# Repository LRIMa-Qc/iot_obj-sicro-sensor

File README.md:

# iot_obj-sicro-sensor

Authors : LRIMa (Laboratoire de Recherche Informatique de Maisonneuve)

## Repo composition

```bash
code/
├── actioneur       (esp32 code)
├── broadcaster     (sensor code [nrf52833])
├── central         (python BLE scanning and ALIVEcode integration)
└── central-nrf     (BLE receiver [nrf52840dongle])
schematic/
├── lrima-main/     (Main board KiCad project)
└── lrima-ground/   (Ground board KiCad project)
models/
└── sensor-casing/  (3D CAD models for enclosure)
```

### Physical device

The schematics and PCB were designed using [KiCad](https://www.kicad.org/) EDA software
There is a protective layer that needs to be applied on the ground part of the pcb to prevent corrosion

## Building

#### Tools needed

- VS Code
- [nRF Connect](https://www.nordicsemi.com/Products/Development-tools/nrf-connect-for-desktop)
- [nRF Connect VS Code extension](https://www.nordicsemi.com/Products/Development-tools/nRF-Connect-for-VS-Code)
- nRF toolchain `v3.2.4`
- nRF SDK `v3.2.4`
- J-Link
- Python 3.8+ (for central application)

#### Broadcaster

##### Preparing the environment

Before building the broadcaster program, you **must** make sure that you changed the `CONFIG_BLE_USER_DEFINED_MAC_ADDR` and the `CONFIG_BLE_USER_DEFINED_NAME` so that they are unique. Note that the `CONFIG_BLE_USER_DEFINED_NAME` must end with a number (ex : 01). If you need mac address, you can use this [mac address generator](https://dnschecker.org/mac-address-generator.php).

##### Building

The broadcaster uses the **sysbuild** system from NCS v3.2.4. To build the program for the nrf52833 using the [nRF Connect VS Code extension](https://www.nordicsemi.com/Products/Development-tools/nRF-Connect-for-VS-Code):

1. Open the broadcaster folder in VS Code
2. Use the nRF Connect extension to build using the `lrima_greenhouse_nrf52833` board
3. Flash using the [extension flashing options](https://nrfconnect.github.io/vscode-nrf-connect/get_started/quick_debug.html#how-to-flash-an-application)

Note: If flashing fails, use the `erase and flash` option to perform a full erase first.

###### J-Link setup

#### Firmware over the air update (DFU)

The board supports over-the-air firmware updates. To prepare an update:

1. Build the application as described above
2. Locate the signed image in the sysbuild app domain: `build/broadcaster/zephyr/zephyr.signed.bin`
3. Transfer this file to your phone
4. Press and hold button1 until the LED is on, then release
5. You will have up to 60 seconds (configurable via `CONFIG_BLE_DFU_ADV_DURATION_SEC`) to start the update
6. Use the [nRF Connect mobile app](https://www.nordicsemi.com/Products/Development-tools/nrf-connect-for-mobile) to connect to the device (named with your `CONFIG_BLE_USER_DEFINED_NAME`)
7. Go to the `DFU` tab and select `zephyr.signed.bin`
8. Press `Upload` and monitor the progress

#### Device Functionality

The broadcaster uses a single BLE advertising workflow. It sends sensor data uplink and then opens a short scan window to receive a downlink sleep update when needed. The user can wake up the device at any time by pressing button1. There is never a connection established, and all communication is done through advertisements and scan responses.

##### Broadcaster

The broadcaster collects sensor data and transmits it BLE advertisements:

**Supported sensors:**

- Temperature/Humidity (SHT4X)
- Soil temperature/moisture/conductivity (STCC4)
- CO2 concentration

**Transmission behavior:**

- Sends data at intervals specified by `CONFIG_SENSOR_SLEEP_DURATION_SEC`
- Uses BLE advertising for the duration specified in `CONFIG_BLE_ADV_DURATION_SEC`
- Publishes a 29-byte service payload containing company ID, node ID, sequence, sleep duration, sensor values, and a presence bitmap
- Opens an active scan window after uplink to receive sleep updates sent by the central
- Beacon payload structure is shown below:

> **Note:** The diagram above predates the latest payload format. See the broadcaster documentation for the full 29-byte layout and presence bitmap details.

### Central-nrf

The central-nrf firmware runs on the nRF52840 dongle to receive BLE broadcasts from the broadcaster.

**Building:**

1. Use the [nRF Connect VS Code extension](https://www.nordicsemi.com/Products/Development-tools/nRF-Connect-for-VS-Code) to build for `nrf52840dongle_nrf52840` board
2. Flash using the nRF Connect for Desktop programmer tools
3. Put the device in [DFU mode](https://infocenter.nordicsemi.com/index.jsp?topic=%2Fug_nrf52840_dongle%2FUG%2Fnrf52840_Dongle%2Fprogramming.html)
4. Flash the `build/zephyr/zephyr.hex` file

### Central (Python Application)

The central application handles BLE scanning, data collection, and integration with ALIVEcode.

**Core modules:**

- `core/storage.py` - Persistent data management
- `core/payload.py` - Sensor data parsing and validation
- `core/aliot_sync.py` - ALIVEcode cloud integration
- `core/downlink_advertiser.py` - BlueZ D-Bus advertiser for sleep-time downlink frames
- `core/health.py` - System health monitoring
- `core/config.py` - Configuration management

**Setup and running:**

1. Plug the Central-nrf dongle into a computer or Raspberry Pi
2. Configure the application:
   - Copy `config.ini.example` to `config.ini`
   - Set your `object_id` and `auth_token` from your [ALIVEcode.ca](https://ALIVEcode.ca) IoT project

3. Install dependencies:

   ```bash
   # For Raspberry Pi 4
   pip install -r requirements_pi4.txt

   # For Raspberry Pi 5
   pip install -r requirements_pi5.txt
   ```

   (Using a Python virtual environment is recommended)

   `dbus-next` is required because downlink sleep updates are emitted through BlueZ D-Bus advertising APIs.

4. Run the application:

   ```bash
   python main.py
   ```

5. Power on the broadcaster devices

The application will automatically scan for broadcaster devices, collecting sensor data and synchronizing with ALIVEcode.
It publishes each node under `/doc/<device_index>` including `/doc/<device_index>/sleep_duration_sec`, and uses `/doc/sleep_time` as the desired target for downlink sleep updates.

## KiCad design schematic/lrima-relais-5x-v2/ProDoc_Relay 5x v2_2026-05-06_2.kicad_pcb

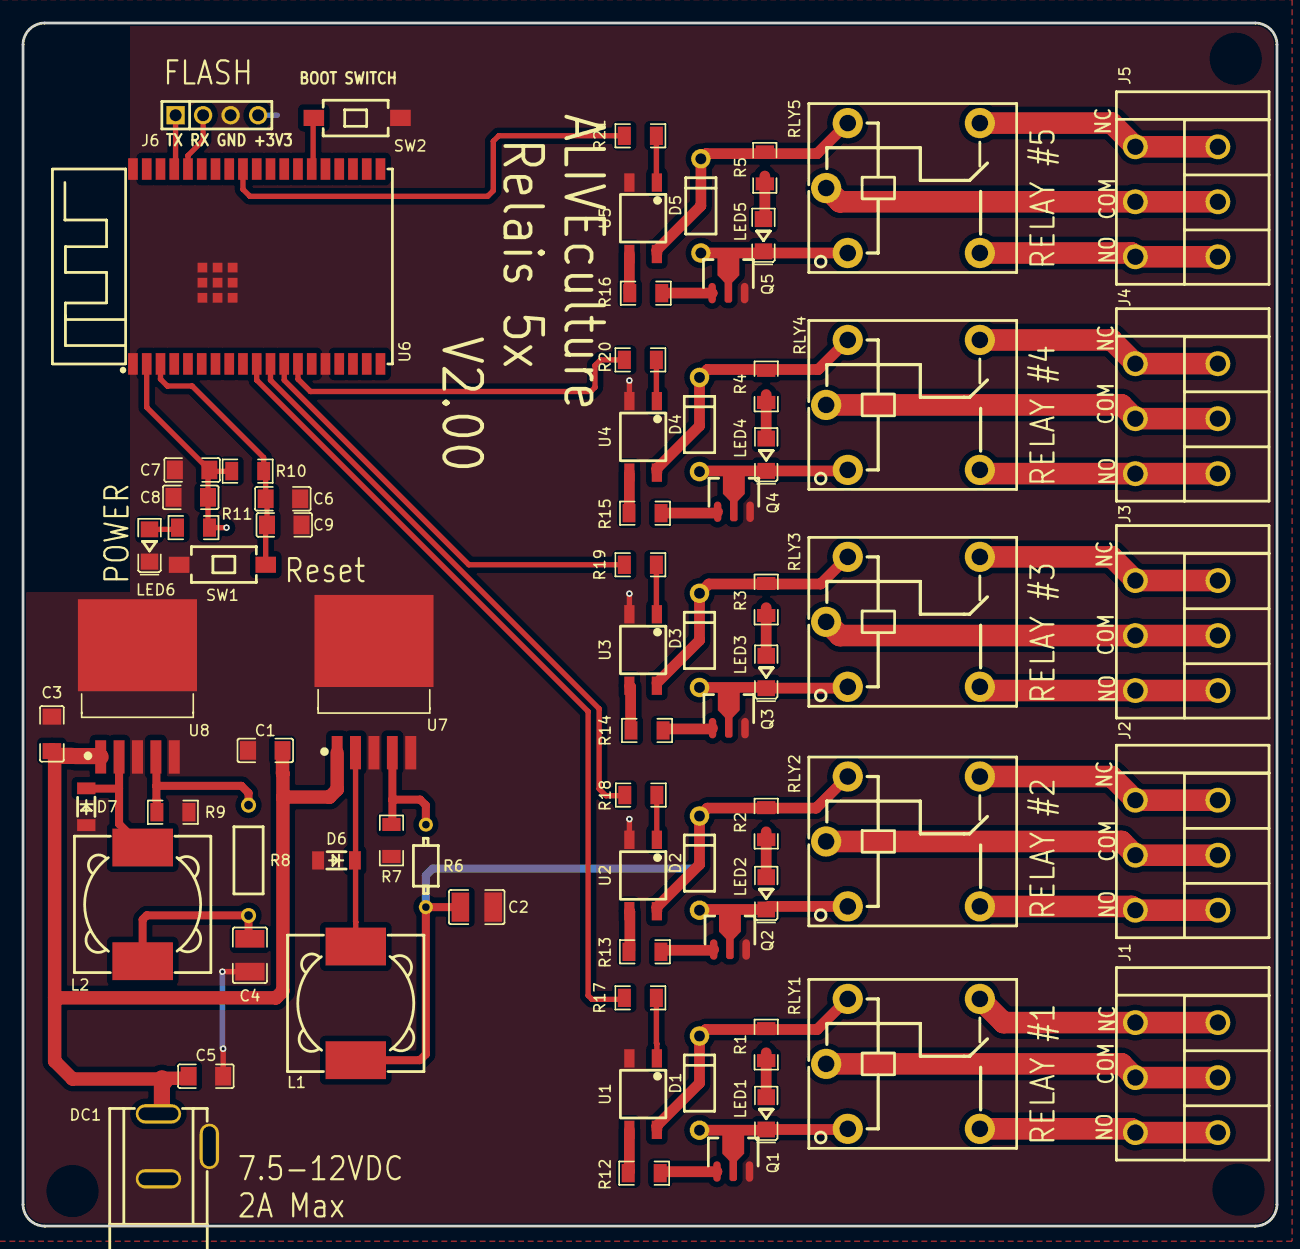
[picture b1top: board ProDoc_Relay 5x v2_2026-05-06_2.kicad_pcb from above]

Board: 2 copper layers, 115.8 x 111.1 mm, 72 parts (0 on the bottom side), 43 nets.

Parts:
C1, C3, C5, C6, C7, C8, C9: C1206
C2, C4: C1210
D1, D2, D3, D4, D5: DO-41_BD2.4-L4.7-P8.70-D0.9-RD
D6, D7: LL-34_L3.5-W1.5-RD
DC1: CONN-TH_DC-005-2.5A-2.0
J1, J2, J3, J4, J5: CONN-TH_3P-P5.08_DIBO_DB142R-5.08-3P
J6: HDR-TH_4P-P2.54-V-M
L1, L2: IND-SMD_L12.5-W12.5_B82477P4XX
LED1, LED2, LED3, LED4, LED5, LED6: LED1206-R-RD_RED
Q1, Q2, Q3, Q4, Q5: SOT-89-3_L4.5-W2.5-P1.50-LS4.2-TR
R1, R2, R3, R4, R5, R7, R9, R10, R11, R12, R13, R14, R15, R16, R17, R18, R19, R20, R21: R1206
R6: RES-TH_BD2.3-L3.7-P7.70-D0.9
R8: RES-TH_BD2.7-L6.2-P10.20-D0.4
RLY1, RLY2, RLY3, RLY4, RLY5: RELAY-TH_SRD-XXVDC-XL-C
SW1, SW2: SW-SMD_L6.0-W3.3-LS8.0
U1, U2, U3, U4, U5: OPTO-SMD-4_L4.4-W4.1-P2.54-LS7.0-TL
U6: WIFI-SMD_ESP32-WROVER-IE8MB
U7, U8: TO-263-5_L10.2-W8.9-P1.70-BR

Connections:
$1N1874: LED1.1, R1.1
$1N2733: LED2.1, R2.1
$1N2848: LED3.1, R3.1
$1N2963: LED4.1, R4.1
$1N3078: LED5.1, R5.1
$1N7448: D6.1, L1.2, U7.2
$1N7557: R6.2, R7.2, U7.4
$1N7965: D7.1, L2.2, U8.2
$1N7972: R8.2, R9.2, U8.4
$1N9867: SW2.1, U6.25
$1N10273: LED6.1, R11.1
$1N20678: R12.1, U1.3
$1N20720: R13.1, U2.3
$1N20762: R14.1, U3.3
$1N20804: R15.1, U4.3
$1N20846: R16.1, U5.3
$1N25591: R17.2, U1.1
$1N25607: R18.2, U2.1
$1N25612: R19.2, U3.1
$1N25623: R20.2, U4.1
$1N25628: R21.2, U5.1
+3V3: C4.1, C7.2, C8.2, J6.4, L2.1, R8.1, R10.2, R11.2, U6.2
+5V: C2.1, D1.1, D2.1, D3.1, D4.1, D5.1, L1.1, R1.2, R2.2, R3.2, R4.2, R5.2, R6.1, RLY1.4, RLY2.4, RLY3.4, RLY4.4, RLY5.4, U1.4, U2.4, U3.4, U4.4, U5.4
GND: C1.1, C2.2, C3.1, C4.2, C5.2, C6.2, C7.1, C8.1, C9.1, D6.2, D7.2, DC1.2, DC1.3, J6.3, LED6.2, Q1.3, Q2.3, Q3.3, Q4.3, Q5.3, R7.1, R9.1, SW1.2, SW2.2, U1.2, U2.2, U3.2, U4.2, U5.2, U6.1, U6.15, U6.38, U7.3, U7.5, U7.6, U8.3, U8.5, U8.6
RE1-ACT: R17.1, U6.10
RE1-COIL: Q1.1, R12.2
RE1-COIL-END: D1.2, LED1.2, Q1.2, RLY1.1
RE2-ACT: R18.1, U6.11
RE2-COIL: Q2.1, R13.2
RE2-COIL-END: D2.2, LED2.2, Q2.2, RLY2.1
RE3-ACT: R19.1, U6.12
RE3-COIL: Q3.1, R14.2
RE3-COIL-END: D3.2, LED3.2, Q3.2, RLY3.1
RE4-ACT: R20.1, U6.13
RE4-COIL: Q4.1, R15.2
RE4-COIL-END: D4.2, LED4.2, Q4.2, RLY4.1
RE5-ACT: R21.1, U6.30
RE5-COIL: Q5.1, R16.2
RE5-COIL-END: D5.2, LED5.2, Q5.2, RLY5.1
RST: C6.1, C9.2, R10.1, SW1.1, U6.3
RX: J6.2, U6.34
TX: J6.1, U6.35
VIN: C1.2, C3.2, C5.1, DC1.1, U7.1, U8.1

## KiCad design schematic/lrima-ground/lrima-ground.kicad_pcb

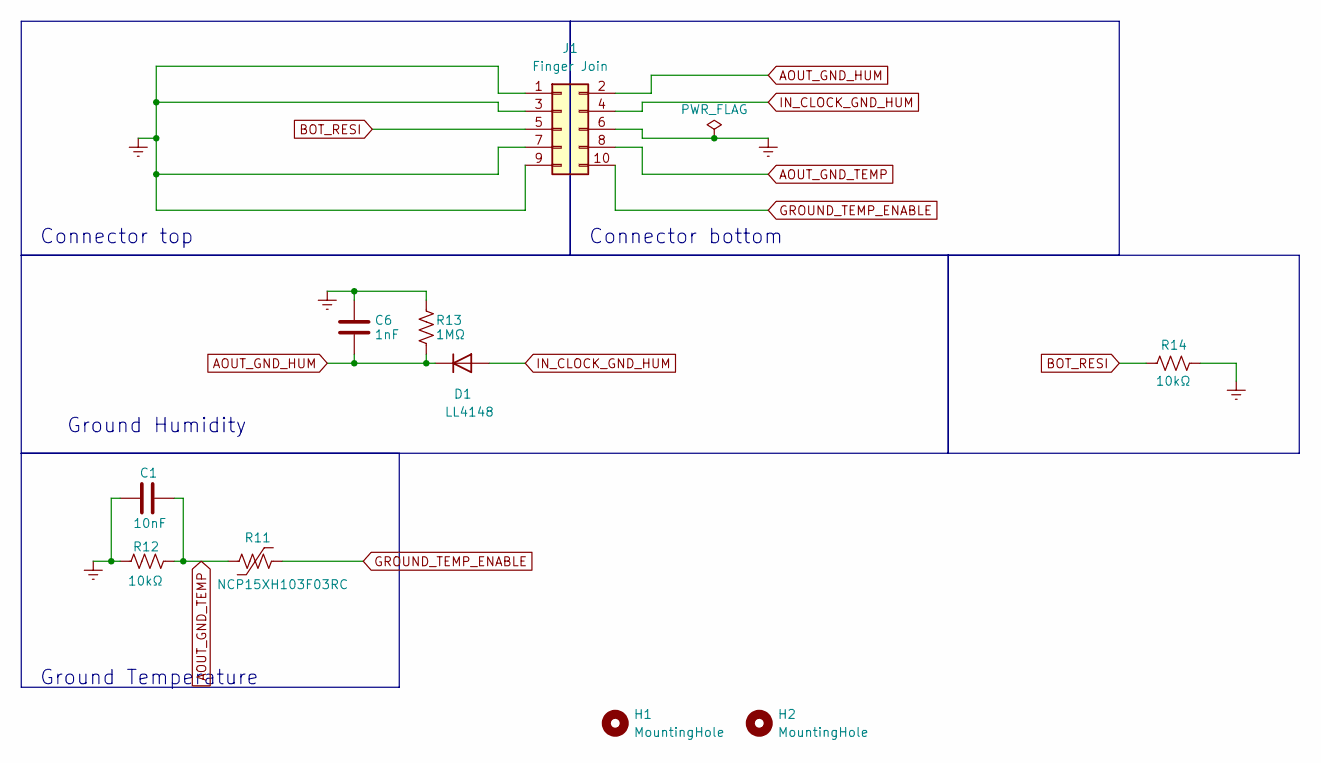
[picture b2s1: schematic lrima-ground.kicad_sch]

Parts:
C1: 10nF; C_0603_1608Metric; Manufacturer Part CC0603KRX7R9BB103; LCSC Part Name 10nF ±10% 50V
C6: 1nF; C_0603_1608Metric; Manufacturer Part CC0603KRX7R9BB102; LCSC Part Name 1nF ±10% 50V
D1: LL4148; D_MiniMELF; Manufacturer Part LL4148; LCSC Part Name 75V 200mA 4ns
H1, H2: MountingHole; MountingHole_3.2mm_M3
J1: Finger Join; Edge_Finger_5P
R11: NCP15XH103F03RC; R_0402_1005Metric; Manufacturer Part NCP15XH103F03RC; LCSC Part Name 10kΩ 电阻精度:±1% 3380K
R12, R14: 10kΩ; R_0603_1608Metric; Manufacturer Part 0603WAF1002T5E; LCSC Part Name 厚膜电阻 10kΩ ±1% 100mW
R13: 1MΩ; R_0603_1608Metric; Manufacturer Part 0603WAF1004T5E; LCSC Part Name 1MΩ ±1% 100mW

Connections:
AOUT_GND_HUM: C6.1, D1.1 (K), J1.2, R13.1
AOUT_GND_TEMP: C1.2, J1.8, R11.1, R12.2
BOT_RESI: J1.5, R14.1
GNDREF: C1.1, C6.2, J1.1, J1.3, J1.6, J1.7, J1.9, R12.1, R13.2, R14.2
GROUND_TEMP_ENABLE: J1.10, R11.2
IN_CLOCK_GND_HUM: D1.2 (A), J1.4

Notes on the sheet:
Ground Temperature
Connector top
Connector bottom
Ground Humidity

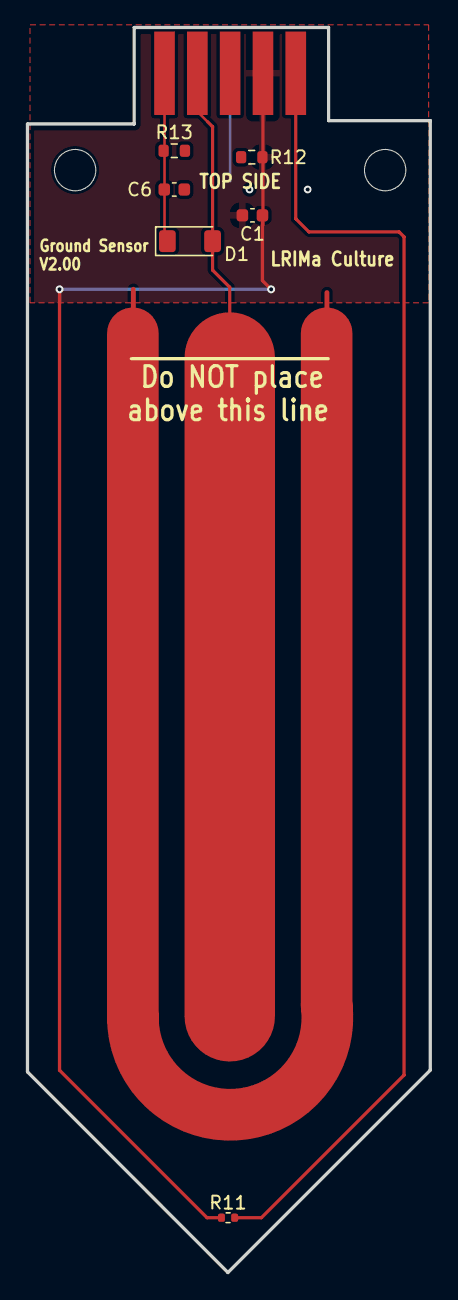
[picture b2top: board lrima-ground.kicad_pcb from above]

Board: 2 copper layers, 31.2 x 96.4 mm, 10 parts (1 on the bottom side), 6 nets.

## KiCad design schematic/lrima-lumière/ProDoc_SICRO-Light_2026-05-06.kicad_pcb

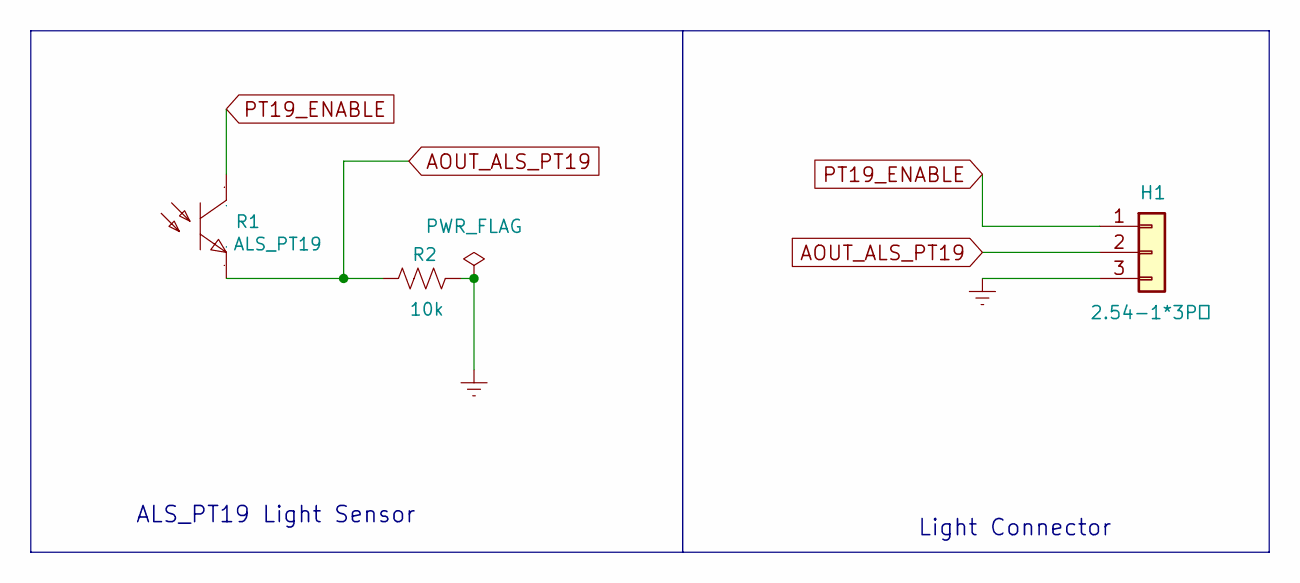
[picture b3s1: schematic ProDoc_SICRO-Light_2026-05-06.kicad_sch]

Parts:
H1: 2.54-1*3P针; HDR-TH_3P-P2.54-V-M-1; Manufacturer Part 2.54-1*3P针; LCSC Part Name 间距:2.54mm 1x3P 直插 方针
R1: ALS_PT19; SENSORS-SMD_ALS-PT19; Manufacturer Part ALS-PT19-315C/L177/TR8
R2: 10k; R0603; Manufacturer Part C25804

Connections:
AOUT_ALS_PT19: H1.2, R1.2, R2.1
GND: H1.3, R2.2
PT19_ENABLE: H1.1, R1.1

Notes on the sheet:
Light Connector
ALS_PT19 Light Sensor

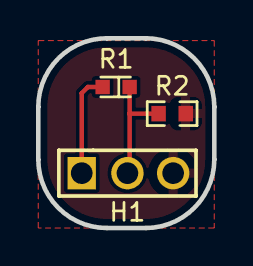
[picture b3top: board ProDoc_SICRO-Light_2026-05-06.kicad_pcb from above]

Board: 2 copper layers, 9.8 x 10.5 mm, 3 parts (0 on the bottom side), 3 nets.

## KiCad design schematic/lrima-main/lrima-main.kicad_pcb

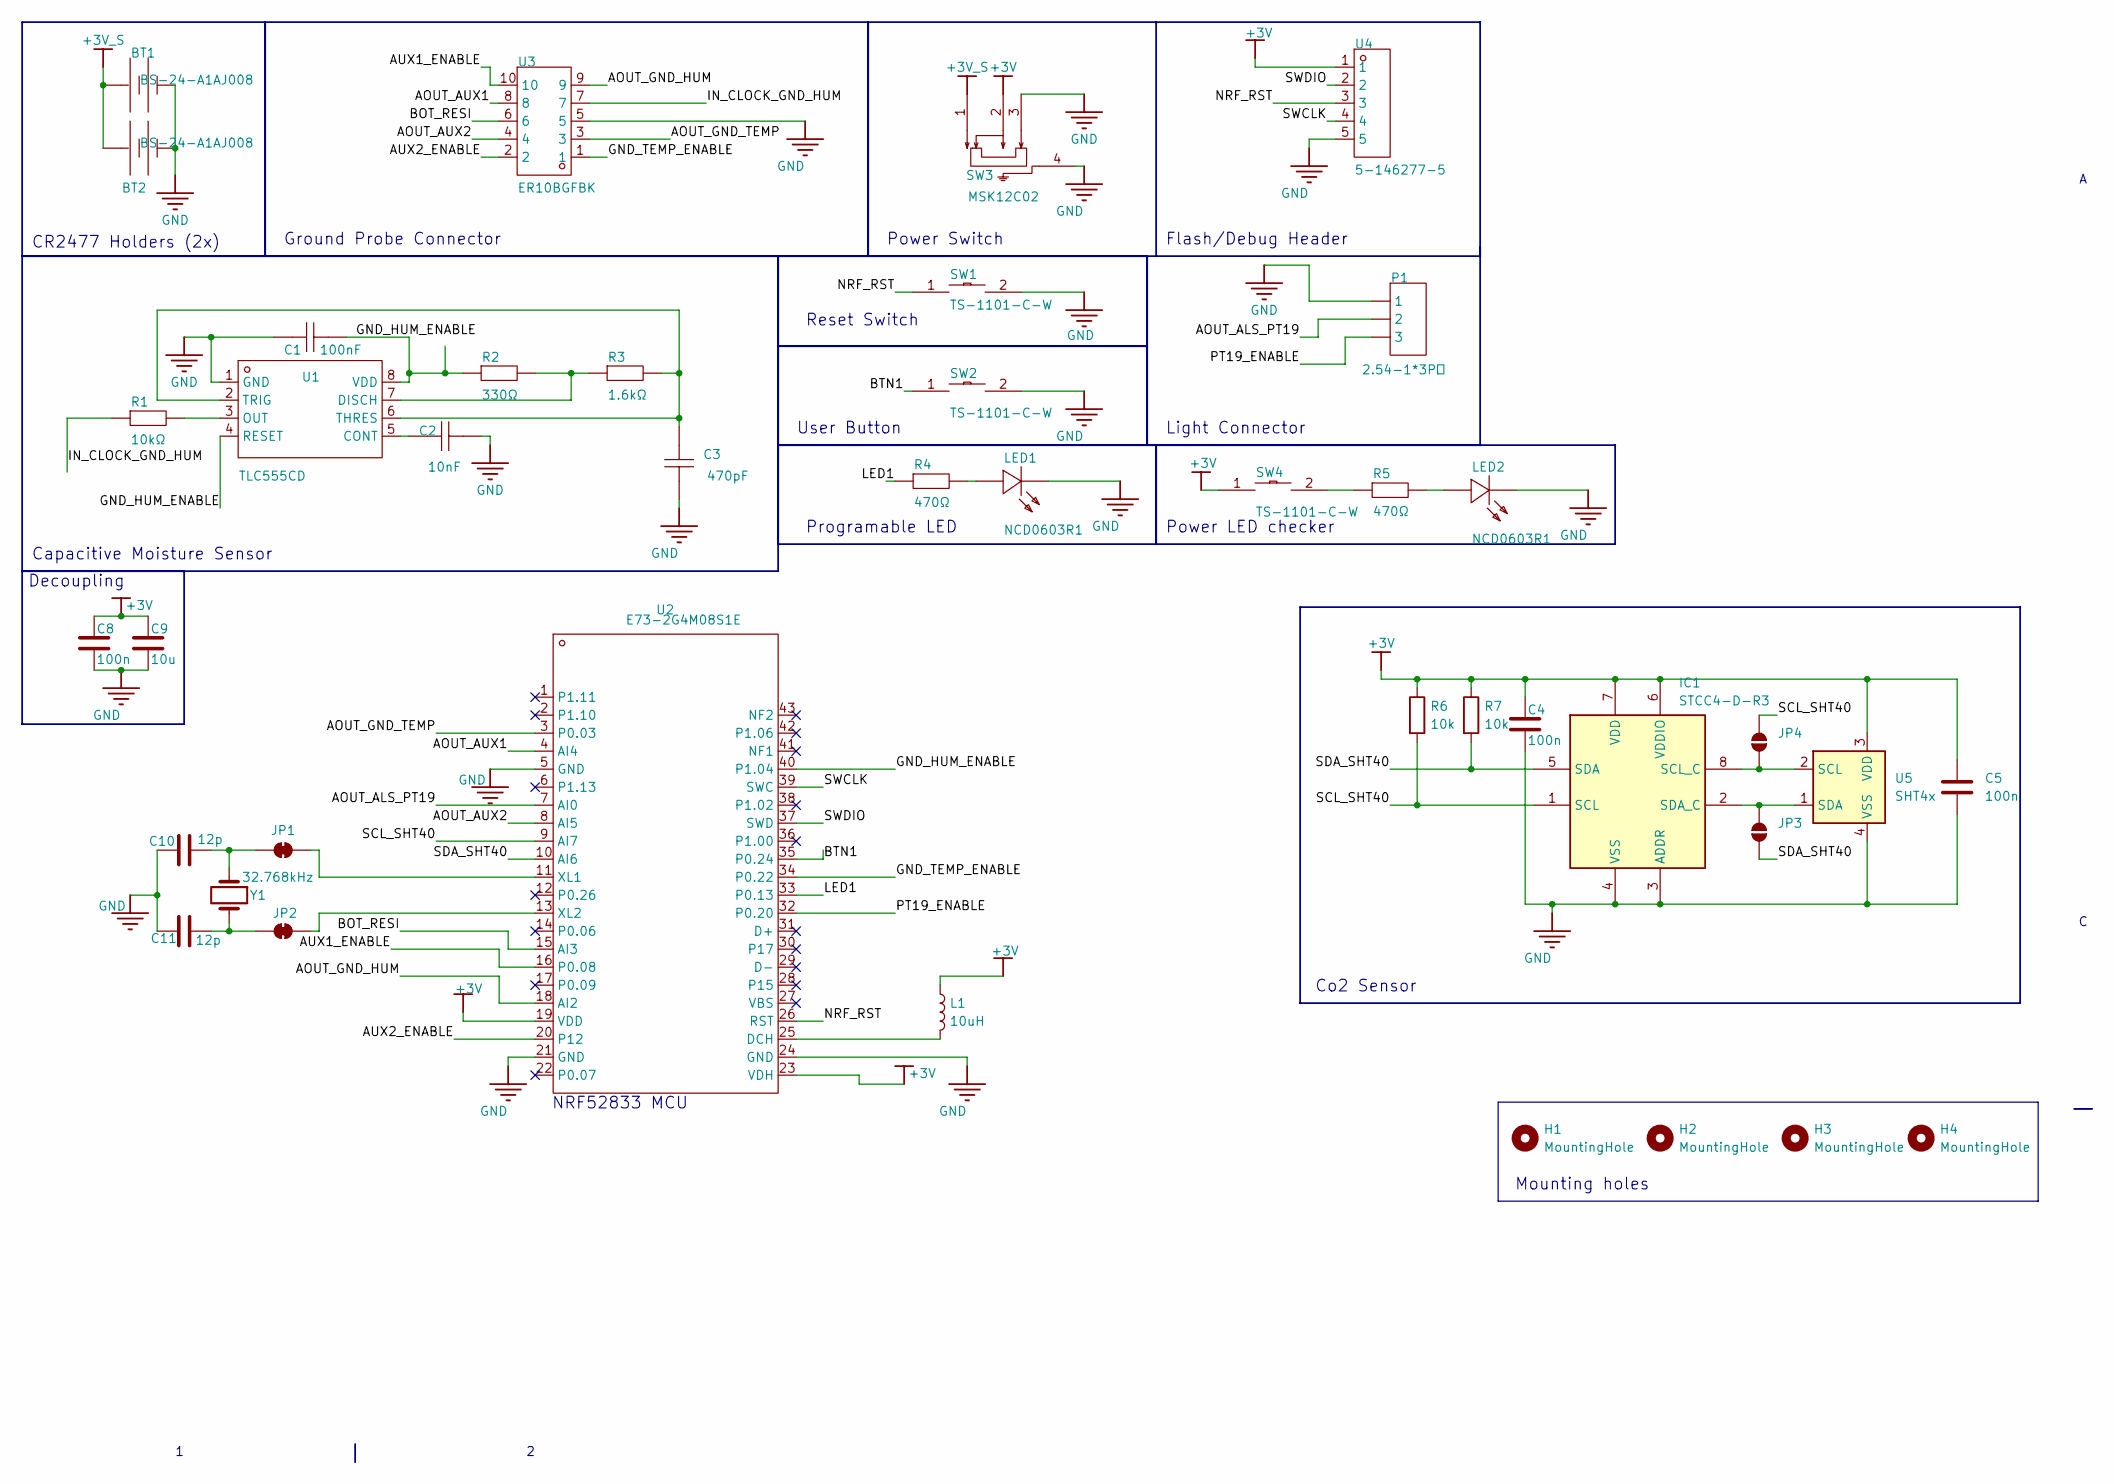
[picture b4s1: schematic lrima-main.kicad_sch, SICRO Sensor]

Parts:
BT1, BT2: BS-24-A1AJ008; BAT-TH_BS-24-A1AJ013; MANUFACTURER PART BS-24-A1AJ008; LCSC PART NAME 电池底座 适用电池:CR2477
C1: 100nF; C_0603_1608Metric_Pad1.08x0.95mm_HandSolder; TOLERANCE ±10%; MANUFACTURER PART 0603B104K500NT; LCSC PART NAME 100nF ±10% 50V
C2: 10nF; C_0603_1608Metric_Pad1.08x0.95mm_HandSolder; TOLERANCE ±10%; MANUFACTURER PART CC0603KRX7R9BB103; LCSC PART NAME 10nF ±10% 50V
C3: 470pF; C_0603_1608Metric_Pad1.08x0.95mm_HandSolder; TOLERANCE ±10%; MANUFACTURER PART 0603B471K500NT; LCSC PART NAME 470pF ±10% 50V
C4, C5, C8: 100n; C_0603_1608Metric_Pad1.08x0.95mm_HandSolder
C9: 10u; C_0603_1608Metric_Pad1.08x0.95mm_HandSolder
C10, C11: 12p; C_0603_1608Metric_Pad1.08x0.95mm_HandSolder
H1, H2, H3, H4: MountingHole; MountingHole_2.2mm_M2
IC1: STCC4-D-R3; STCC4DR3; Manufacturer_Part_Number STCC4-D-R3
JP1, JP2: SolderJumper-2_P1.3mm_Bridged_RoundedPad1.0x1.5mm
JP3, JP4: SolderJumper-2_P1.3mm_Open_RoundedPad1.0x1.5mm
L1: 10uH; L_0603_1608Metric
LED1, LED2: NCD0603R1; LED_0603_1608Metric_Pad1.05x0.95mm_HandSolder; MANUFACTURER PART NCD0603R1; LCSC PART NAME 红灯
P1: 2.54-1*3P母; PinHeader_1x03_P2.54mm_Horizontal; MANUFACTURER PART 2.54-1*3P母; JLCPCB PART CLASS Extended Part
R1: 10kΩ; R_0603_1608Metric_Pad0.98x0.95mm_HandSolder; TOLERANCE ±1%; MANUFACTURER PART 0603WAF1002T5E; LCSC PART NAME 厚膜电阻 10kΩ ±1% 100mW
R2: 330Ω; R_0603_1608Metric_Pad0.98x0.95mm_HandSolder; TOLERANCE ±1%; MANUFACTURER PART SCR0603F330R; LCSC PART NAME 330Ω ±1%
R3: 1.6kΩ; R_0603_1608Metric_Pad0.98x0.95mm_HandSolder; TOLERANCE ±1%; MANUFACTURER PART 0603WAF1601T5E; LCSC PART NAME 1.6kΩ ±1% 100mW
R4, R5: 470Ω; R_0603_1608Metric_Pad0.98x0.95mm_HandSolder; TOLERANCE ±1%; MANUFACTURER PART 0603WAF4700T5E; LCSC PART NAME 470Ω ±1% 100mW
R6, R7: 10k; R_0603_1608Metric_Pad0.98x0.95mm_HandSolder
SW1, SW2, SW4: TS-1101-C-W; SW-SMD_L6.0-W3.3-LS8.0; VOLTAGE RATING (DC) 12V; MANUFACTURER PART TS-1101-C-W; LCSC PART NAME 立贴 6*3.6*2.5mm 轻触开关 一型3*6*2.5有白ZD b拉伸白色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
SW3: MSK12C02; SW_SPDT_PCM12; MANUFACTURER PART MSK12C02; LCSC PART NAME 两档侧拨贴片 7脚 拨动 白柄 柄长1.5mm,带定位柱
U1: TLC555CD; SOIC-8_3.9x4.9mm_P1.27mm; SUPPLY VOLTAGE 2V~15V; MANUFACTURER PART TLC555CD; LCSC PART NAME 2V~15V
U2: NRF_RST; WIRELM-SMD_E73-2G4M08S1C; MANUFACTURER PART E73-2G4M08S1E; JLCPCB PART CLASS Extended Part
U3: ER10BGFBK; CONN-TH_10P-P2.54_WINGTAT_ER10BGFBK; MANUFACTURER PART ER10BGFBK; JLCPCB PART CLASS Extended Part
U4: 5-146277-5; PinHeader_1x05_P2.54mm_Vertical; CURRENT RATING (MAX) 3A; MANUFACTURER PART 5-146277-5; LCSC PART NAME 间距:2.54mm 直插
U5: SHT4x; SHT4X
Y1: 32.768kHz; Crystal_SMD_3215-2Pin_3.2x1.5mm

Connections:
+3V: C4.1, C5.1, C8.1, C9.1, IC1.6 (VDDIO), IC1.7 (VDD), L1.1, R6.1, R7.1, SW3.2, SW4.1, U2.19 (VDD), U2.23 (VDH), U4.1, U5.3 (VDD)
+3V_S: BT1.1 (+), BT2.1 (+), SW3.1
/AOUT_ALS_PT19: P1.2, U2.7 (AI0)
/AOUT_AUX1: U2.4 (AI4), U3.8
/AOUT_AUX2: U2.8 (AI5), U3.4
/AOUT_GND_HUM: U2.18 (AI2), U3.9
/AOUT_GND_TEMP: U2.3 (P0.03), U3.3
/AUX1_ENABLE: U2.16 (P0.08), U3.10
/AUX2_ENABLE: U2.20 (P12), U3.2
/BOT_RESI: U2.15 (AI3), U3.6
/BTN1: SW2.1, U2.35 (P0.24); also elsewhere on the board
/GND_HUM_ENABLE: C1.1, R2.2, U1.4 (RESET), U1.8 (VDD), U2.40 (P1.04)
/GND_TEMP_ENABLE: U2.34 (P0.22), U3.1
/IN_CLOCK_GND_HUM: R1.1, U3.7
/LED1: R4.1, U2.33 (P0.13)
/NRF_RST: SW1.1, U2.26 (RST), U4.3; also elsewhere on the board
/PT19_ENABLE: P1.3, U2.32 (P0.20)
/SCL_SHT40: IC1.1 (SCL), JP4.2 (B), R6.2, U2.9 (AI7)
/SDA_SHT40: IC1.5 (SDA), JP3.1 (A), R7.2, U2.10 (AI6)
/SWCLK: U2.39 (SWC), U4.4
/SWDIO: U2.37 (SWD), U4.2
GND: BT1.2 (-), BT2.2 (-), C1.2, C2.1, C3.2, C4.2, C5.2, C8.2, C9.2, C10.2, C11.2, IC1.3 (ADDR), IC1.4 (VSS), LED1.1 (K), LED2.1 (K), P1.1, SW1.2, SW2.2, SW3.3, SW3.4, U1.1 (GND), U2.5 (GND), U2.21 (GND), U2.24 (GND), U3.5, U4.5, U5.4 (VSS); also elsewhere on the board
unnamed: IC1.8 (SCL_C), JP4.1 (A), U5.2 (SCL)
unnamed: IC1.2 (SDA_C), JP3.2 (B), U5.1 (SDA)
unnamed: JP1.1 (A), U2.11 (XL1)
unnamed: C10.1, JP1.2 (B), Y1.1
unnamed: JP2.1 (A), U2.13 (XL2)
unnamed: C11.1, JP2.2 (B), Y1.2
unnamed: LED1.2 (A), R4.2
unnamed: LED2.2 (A), R5.2
unnamed: R5.1, SW4.2
unnamed: C2.2, U1.5 (CONT)
unnamed: R2.1, R3.2, U1.7 (DISCH)
unnamed: R1.2, U1.3 (OUT)
unnamed: C3.1, R3.1, U1.2 (TRIG), U1.6 (THRES)
unnamed: L1.2, U2.25 (DCH)

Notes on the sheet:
Programable LED
Light Connector
Power Switch
Decoupling
Power LED checker
Capacitive Moisture Sensor
Mounting holes
Ground Probe Connector
Flash/Debug Header
Co2 Sensor
CR2477 Holders (2x)
NRF52833 MCU
User Button
Reset Switch

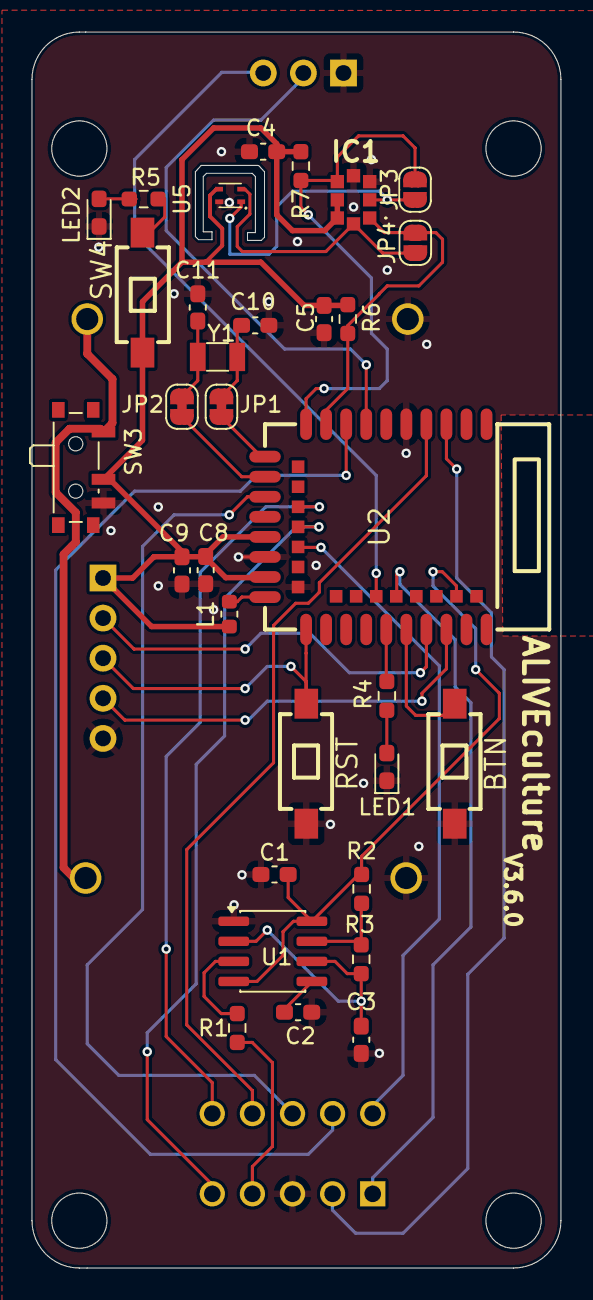
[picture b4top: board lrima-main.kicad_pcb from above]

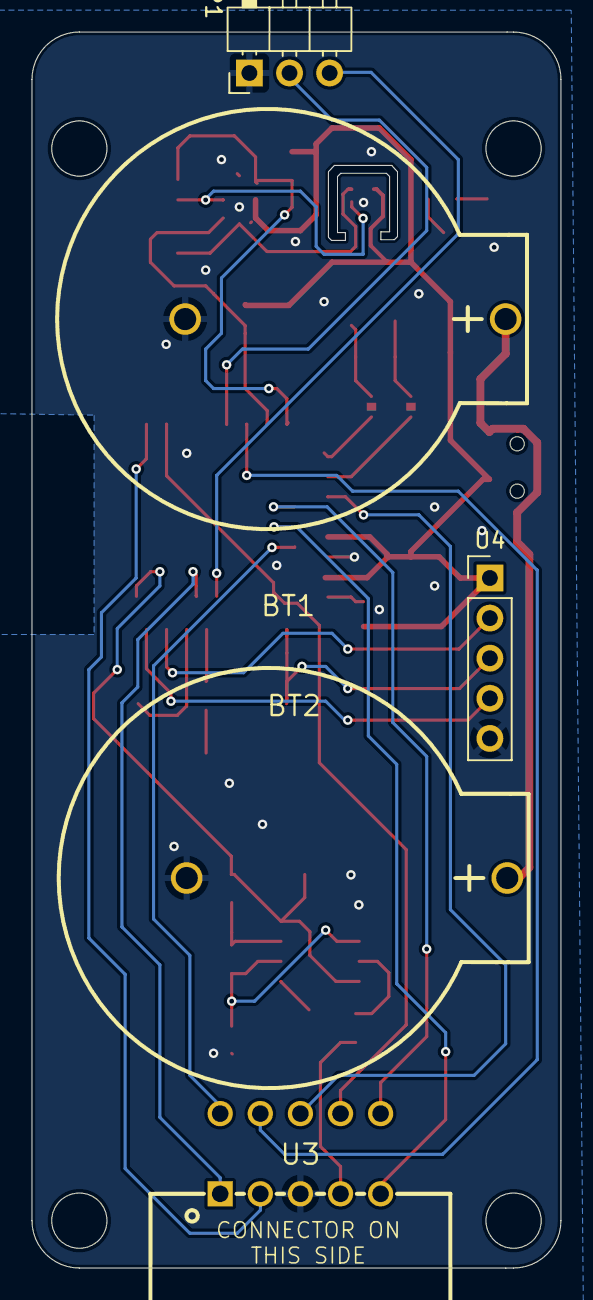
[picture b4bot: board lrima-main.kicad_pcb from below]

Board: 2 copper layers, 33.5 x 78.3 mm, 41 parts (5 on the bottom side), 36 nets.

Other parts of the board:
BTN: TS-1101-C-W; SW-SMD_L6.0-W3.3-LS8.0
RST: TS-1101-C-W; SW-SMD_L6.0-W3.3-LS8.0

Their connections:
/BTN1: BTN.1; also elsewhere on the board
/NRF_RST: RST.1; also elsewhere on the board
GND: BTN.2, RST.2; also elsewhere on the board

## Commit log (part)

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2023-06-26 ADD - python ble to ALIVEcode scripts
2023-06-26 ADD - nrf52840dongle script to receive BLE packets
2023-06-26 ADD - sensor code for nrf52833
2023-06-26 MOVE - all code in code folder
2023-06-26 ADD - schematic for the sensor
2023-06-26 FIX - python not trying to reconnect
2023-06-27 FIX - messages where not sending negative values
2023-06-27 MOD - only send data if a values is changed
2023-11-21 MOD : Updated board config
2023-11-29 FIX : Flashing firmware
2023-11-29 ADD : Central is now printing the current value on the pi
2023-11-29 FIX - extra ()
2023-12-06 MOD : Logs are not fetch every time
2023-12-06 FIX : High data usage for sending logs
2023-12-06 ADD : Mac address filtering
2023-12-07 FIX : Constant name
2023-12-20 MOD : Updated READme
2023-12-21 MOD : Higher GND Hum sensibility
2023-12-21 ADD : GND_HUM_V1 calibrated
2023-12-22 ADD : Link to how to flash
2023-12-22 MOD : Added sdk version
2023-12-22 MOD : Add link in readme
2023-12-29 MOD : Added filter for "^["
2023-12-29 ADD : Adding more log inf on the main loop
2023-12-30 ADD : Sleep for aht20 init
2024-01-02 code quon a flash sur les capteurs qui marche
2024-01-04 ADD - STH20 Drivers
2024-01-05 modification main to do with bluetooth
2024-01-05 modification device + add bleakScanning to do with bluetooth
2024-01-05 trying to fix the start bleak loop
2024-01-06 ADD : GATT service to edit the sleep time via BLE
2024-01-06 MOD : Code refactor
2024-01-06 ADD : Idle timeout
2024-01-06 Add - I2C scanner and automatic sht/aht detection
2024-01-07 FIX : Checking mac sleep duration
2024-01-08 ADD : LED and Button drivers
2024-01-08 ADD : Button to wake up and Start DFU
2024-01-08 ADD : More time when the DFU is enabled
2024-01-08 REM- unused code
2024-01-09 FIX : AHT20 not reading
2024-01-16 ADD - Works with change sleep time
2024-01-16 FIX - round values before pushing to alivecode
2024-01-17 MOD : New device index
2024-01-18 MOD : Sensor sleep on disconection
2024-01-18 MOD : Merge two BLE Broadcast
2024-01-18 FIX - bluetooth connection and changed lrimaconn -> lrima
2024-01-19 REM - unused configs
2024-01-19 ADD : Dongle Myrio support via UART
2024-01-22 MOD : CTS P0.16 -> P0.13 RTS P1.01 -> P1.10
2024-01-22 MOD : Disable UART RX
2024-01-22 changed err handling a bit
2024-01-23 ADD - gitignore pycache central
2024-01-23 added offline mode
2024-01-23 ADD : Code pour l'actionneur
2024-01-23 ADD : Support for coded PHY on broadcaster
2024-01-24 FIX : Actionneur
2024-01-24 MOD : Auto switch i2c and ADD : SHT21 SHT31
2024-01-24 ADD - readme
2024-01-24 MOD - readme central
2024-01-24 ADD : Support for multiple relays
2024-01-24 MOD : Readme actioneur
2024-01-24 FIX : typo in actioneur README
2024-01-24 MOD - pathname for PM2 default to PATH
2024-01-24 ADD - automatic hci configuration if not defined
2024-01-24 FIX - python path
2024-01-24 MOD : Refactor a bit the actioneur
2024-01-24 FIX - python err
2024-01-24 FIX - python err again
2024-01-25 MOD - PRINTS for central
2024-01-25 MOD : DFU mode on until button released
2024-01-25 MOD : Broadcaster Readme
2024-01-26 from slep tim form 5 to 30
2024-01-26 changez le configue
2024-05-02 CC-BY Licence
2024-05-03 ADD : new schematics versions
2024-07-02 ADD : AliveCode in actionneur readme
2024-07-08 ADD - Changes made from rasp centrale
2024-07-08 ADD - Useful scripts for setup and debugging
2024-07-08 MOD : delay before i2c init
2024-07-22 FIX - Bug with ksleep before init aht
2024-07-30 MOD - READme with new JTAG pictures
2024-07-30 MOD - Calibration values
2024-07-31 MOD - Inverted coefficient order in overlay
2024-08-08 ADD - Console log for ble adapter
2024-08-08 FIX - Not receiving data from sensor when it has been reset
2024-11-05 FIX - Bluetooth enabling bug
2024-11-05 FIX - Opencv version bug
2024-11-06 ADD : 5 Relay Board
2024-11-06 FIX : Mistake in 5 relay implementation
2024-11-24 ADD - 3D model for sensor casing
2024-11-25 Add fusion models of sensor casing
2024-11-26 Add bottom and top part of sicro-sensor casing
2024-11-29 FIX : Inverted Relays
2024-11-29 MOD : Updated actionneur readme
2024-12-10 ADD - Branchements dans le READme
2024-12-15 Add files via upload
    These are the new version of the sensor-casig as of the 15th of december do not print the bottom file with support or the ground will not fit
2025-01-11 Correction des modèles (mesures)
2025-01-13 MOD - Readme of actionneur
2025-01-16 MOD : Better ground temp reading
2025-01-18 ADD - Sleep value will now be always up to date
2025-01-18 DEL - config.ini is now a secret
2025-01-18 FIX - Sleep value is not changed if not connected to ALIVEcode
2025-01-18 ADD - Reboot after not receiving data for 24h
2025-01-20 Fix SECRET.h .example
2025-01-21 Camera controls
2025-01-21 Add reboot after a week to the sensor code
2025-01-22 UpdateDoc only when the function setValveState is called
2025-01-23 ADD - Central additional reboot fallback
2025-01-23 MOD - Reset timer for central updated from 24hr to 12hr
2025-01-23 ADD - Better hciconfig scannera && ADD - Rasp5 pip requirements
2025-01-23 FIX - Console log spam
2025-01-24 Add reboot after a week for the broadcaster
2025-01-24 Cases testés et fonctionnels
2025-02-05 Revert changes for the broadcaster
2025-02-05 ADD - Data.csv to gitignore
2025-02-11 version 11 fev
2025-04-18 Restore TopPart3.stl after case reset
2025-04-20 FIX : Scanning stopping issue
    MOD: readme to install BlueZ 5.82
    REM: sudo reboot
    ADD: restart of the pm2 and bluetooth driver
    CLEAN: BleakScanning
    FIX: Conneciton issues
2025-04-20 REM: Ignoring empty address message
2025-04-20 FORMAT: Code is now formated
2025-04-20 REM : Bad files
2025-04-20 FIX : Lib name
2025-04-20 FIX : Issue in queue
2025-04-20 HANDLE: Connection closed error
2025-04-22 MOD : Restart after inactivity
2025-04-22 MOD : Quit central after reboot
2025-05-16 FIX : add import sys in bleak scanning
2025-05-19 REM : last_received_time.txt
2025-05-19 FIX : last received time
2025-05-19 FIX : time in bleakScanning
2026-01-31 feat(pcb): Add kicad version of main and ground board
2026-01-31 fix(pcb): Changed ALIVE to LRIMa
2026-03-29 feat: migrate broadcaster from NCS 2.4 to 3.2.4 (sysbuild + board + DFU)
    move project to NCS 3.2.4 toolchain/build flow and sysbuild-based multi-image setup
    add/update custom board definition for lrima_greenhouse_nrf52833/nrf52833
    migrate MCUboot configuration to sysbuild-level options and image-local mcuboot config
    switch app/DFU configuration to current MCUmgr transport options
    adopt VERSION-based MCUboot image versioning (drop legacy image-version config usage)
    align DTS/I2C configuration with current nRF TWIM usage
2026-03-29 feat: add SHT4X and STCC4 sensor support with logging configuration
2026-03-29 refactor: clean up formatting and include order in various files
2026-03-29 feat: add CO2 sensor support and update data handling in main application
2026-03-29 feat: implement last received time normalization and improve CSV handling
2026-03-29 feat: Enhance buffer management and restart command handling in scanning and health modules
2026-03-29 feat: Update bleak dependency version and enhance scanner initialization with GATT error handling
2026-03-29 feat: Update README for clarity on project structure, building instructions, and firmware update process
2026-04-04 refactor: Clean up Kconfig and configuration files, remove unused DFU settings and optimize memory allocation
2026-04-04 feat: Implement persistent sleep time settings with loading and saving functionality
2026-04-04 feat: Enhance broadcaster functionality with payload encoding and BLE state management
    - Added payload encoding module for BLE advertisement data in `payload.c` and `payload.h`.
    - Introduced BLE state machine in `ble.h` and implemented state transitions in `ble.c`.
    - Updated `CMakeLists.txt` to include new source files for payload handling.
    - Enhanced button driver to utilize semaphore for button press events.
    - Improved main application logic to handle sleep time and button press more effectively.
    - Created separate debug and release configurations for optimized builds.
2026-04-04 feat: Update LED driver initialization and error handling; add SHTC3 sensor configuration
2026-04-04 fix: Correct indentation for SHTC3 sensor configuration in overlay file
2026-04-04 feat: Update BLE connection handling and improve sleep time settings persistence logging
2026-04-04 feat: Implement application settings persistence for sleep time, device name, and MAC address
2026-04-04 docs: Update README with details on persisted settings and erase/flash procedure
2026-04-04 fix: Improve error handling and logging for sensor readings in the read function
2026-04-06 fix: Enhance error handling for sensor readings and improve logging
2026-04-06 fix: Fix BLE payload decoding by prepending company ID bytes
    The Bleak BLE scanner provides service_data as a dictionary where:
    - Key: Company ID (0x0059)
    - Value: Service data bytes (without company ID)
    The SensorPayloadDecoder expected the full 25-byte payload with company ID
    at indices [0:2]. When the decoder received only 23 bytes of data without
    the company ID, the company ID check failed (0x0043 != 0x0059), causing it
2026-04-06 Refactor BLE data handling and downlink advertisement for sleep updates
    - Updated the main.c file to handle new payload structure and added checks for present data bits.
    - Enhanced bleakScanning.py to manage sleep updates via downlink advertisements.
    - Modified aliot_sync.py to ensure proper handling of sleep time values.
    - Adjusted config.py to include new constants for downlink advertisements.
    - Expanded payload.py to decode new sensor data formats and handle legacy payloads.
    - Updated device.py to manage sleep duration and ensure proper data filtering.
2026-04-06 fix: Update device sleep attribute to sleep_duration_sec for consistency
2026-04-07 fix: Update README files for clarity on firmware updates and downlink sleep handling
2026-04-07 fix: Update BLE configuration and sensor defaults for consistency
2026-04-07 fix: Update device name validation in detection callback
2026-04-08 fix: Update STCC4 driver to support periodic conditioning and sleep management
2026-04-08 fix: Implement LED blink functionality during initialization
2026-04-08 fix: Correct restart_delay format in PM2 configuration
2026-04-08 fix: Update device node ID handling in BLE driver
2026-04-08 fix: Update logging levels and add sensor status handling in STCC4 driver
2026-05-06 Update for schematic bom
2026-06-01 fix: dependecy issue on rasp 4
2026-06-07 feat: add logic for automatic installation
2026-06-07 fix: constrain BLE node ID to uint8 range
2026-06-07 Fix: typo in lrima name
2026-06-07 Apply suggestions from code review
2026-06-07 fix: added sugested changes.
2026-06-08 feat: add logic for automatic installation (#11)
    * feat: add logic for automatic installation
    * Fix: typo in lrima name
    * Apply suggestions from code review
    * fix: added sugested changes.
    ---------
2026-06-08 simple script for camera interaction from web requests through pm2
2026-06-08 ADD - Data receive indicator
2026-06-08 FIX - Import led_control
2026-06-08 feat: added setup script that might or might not work for camera dependencies and configs
2026-06-08 feat: add function to blink LED1 for a specified duration
2026-06-12 fix: replace pm2 with systemd
    NOT BACKWARDS COMPATIBLE, only works with newer centrals using current
    systemd services.
2026-06-12 removed pm2.json
2026-06-12 feat: added trying to change permission of writtable path in LedControl
2026-06-12 fix: forgor groop
2026-06-12 sdaasdasdasdasd
2026-06-12 fix: so turns out ya can't change ownership of /sys files...
2026-06-12 fix: changed path (first one is a symlink to current)
2026-06-12 fix: william est fou
